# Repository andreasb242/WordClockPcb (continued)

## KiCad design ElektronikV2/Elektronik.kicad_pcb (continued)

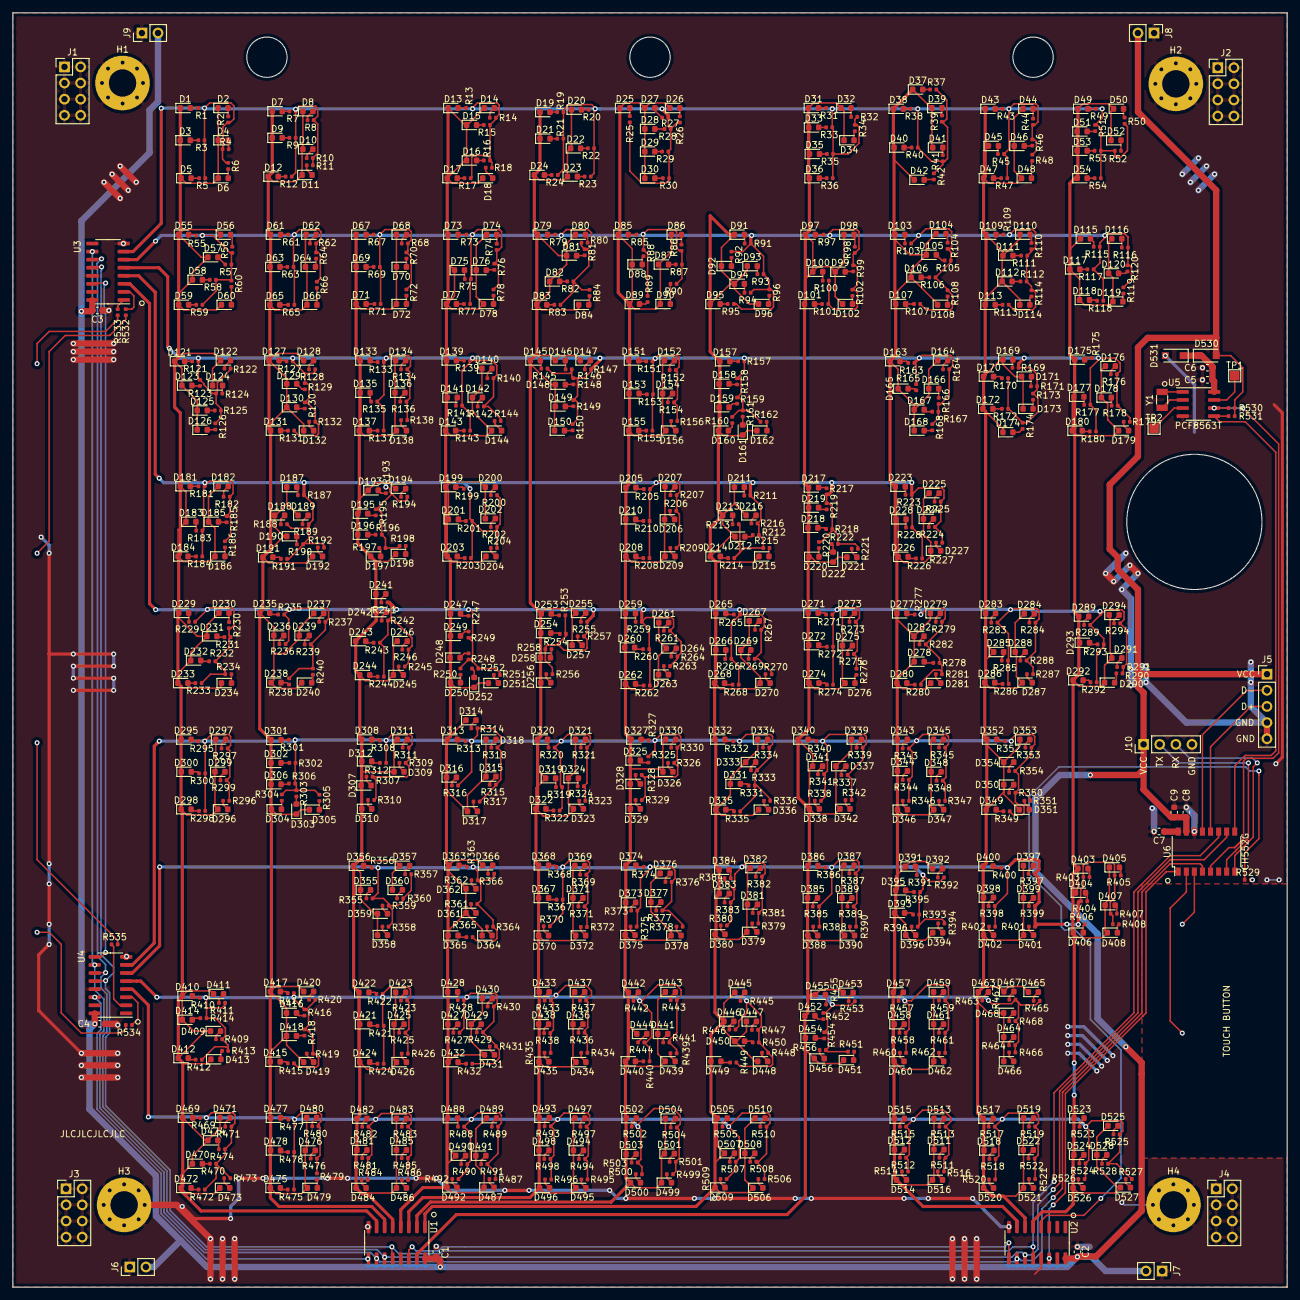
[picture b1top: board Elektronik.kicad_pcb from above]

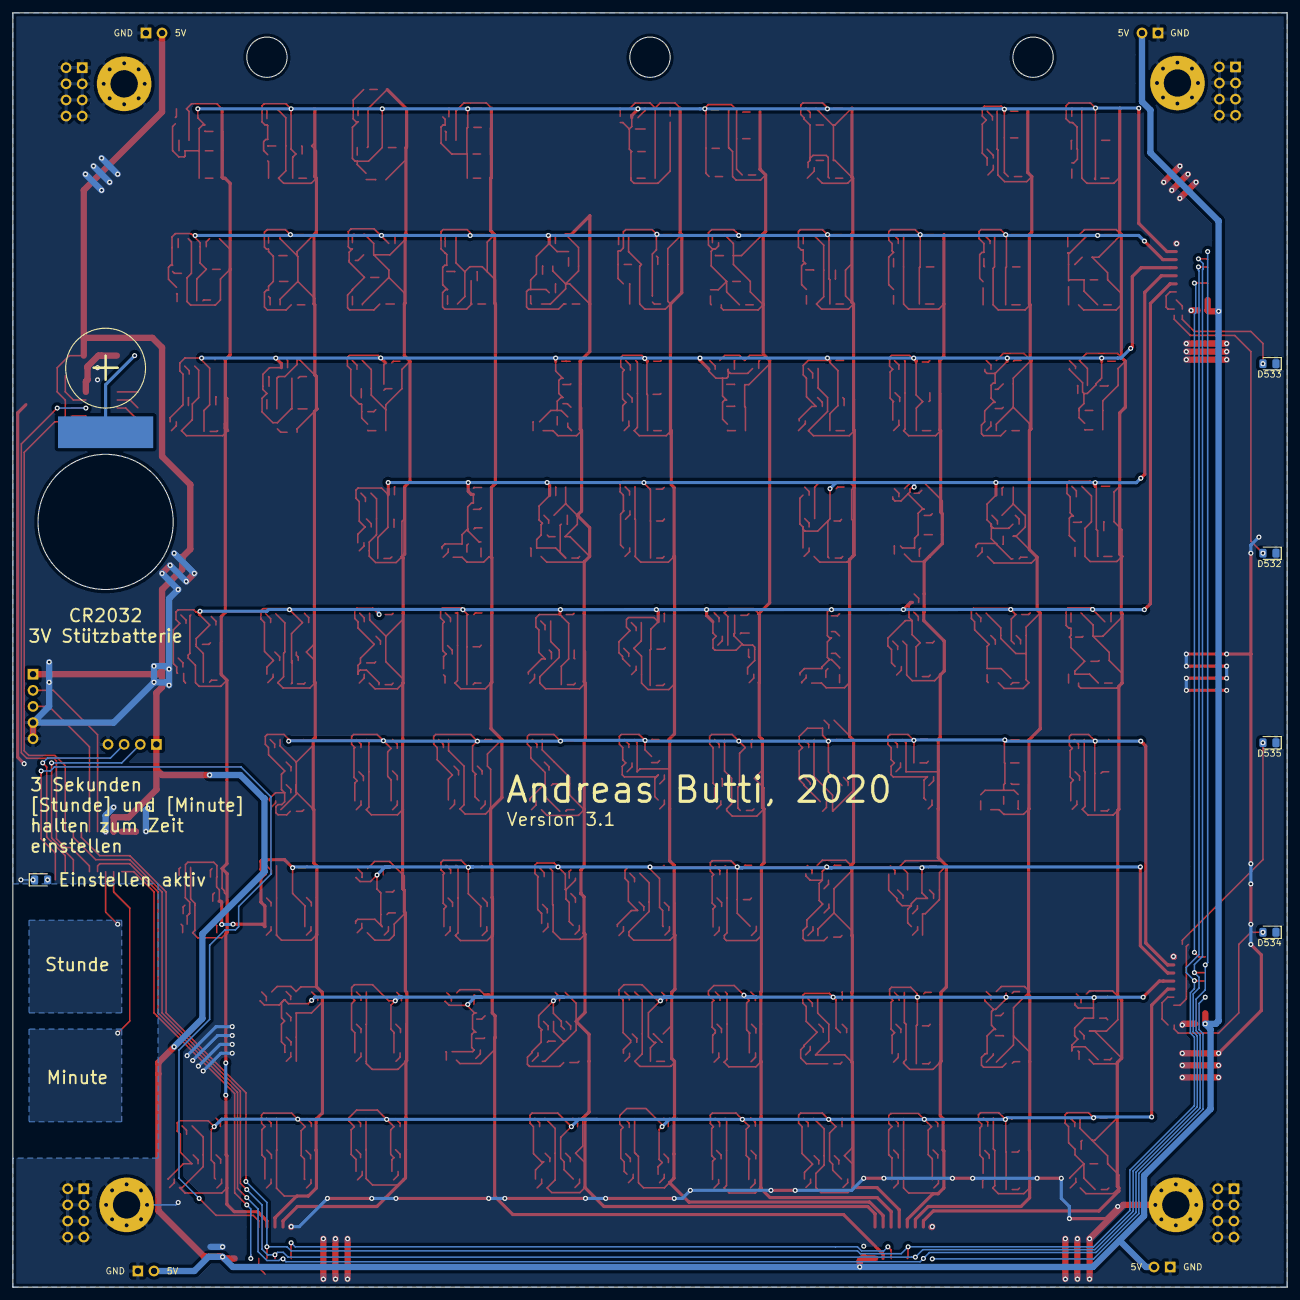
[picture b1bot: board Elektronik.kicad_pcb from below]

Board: 2 copper layers, 200.7 x 200.7 mm, 1104 parts (6 on the bottom side), 580 nets.

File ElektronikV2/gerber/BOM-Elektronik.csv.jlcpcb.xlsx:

Comment | Designator | Footprint | LCSC Part #（optional）
Conn_01x04 | J10 | PinHeader_1x04_P2.54mm_Vertical | x
1kΩ | R535,R534,R533,R532,R529 | R_0402_1005Metric | C11702
blue | D535,D534,D533,D532,D529 | LED_0805_2012Metric_Pad1.15x1.40mm_HandSolder | C72041
CH552G | U6 | SOP-16_4.4x10.4mm_P1.27mm | C111292
Conn_01x02_Male | J9,J8,J7,J6 | PinHeader_1x02_P2.54mm_Vertical | x
Conn_01x05_Male | J5 | PinHeader_1x05_P2.54mm_Vertical | x
1uF | C9,C6 | C_0603_1608Metric | C15849
100nF | C8,C7,C5,C4,C3,C2,C1 | C_0603_1608Metric | C14663
TestPoint | TP3,TP2,TP1 | TestPoint_Pad_1.5x1.5mm
Crystal | Y1 | Crystal_SMD_3215-2Pin_3.2x1.5mm
PCF8563T | U5 | SOIC-8_3.9x4.9mm_P1.27mm | C7440
4.7kΩ | R531,R530 | R_0402_1005Metric | C25900
SM4007PL | D531,D530 | D_SOD-123F | C64898
Rled | R408,R407,R406,R405,R404,R403,R528,R527,R526,R525,R524,R523,R522,R521,R520,R519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 | R_0402_1005Metric
LEDCLOCK | D408,D407,D406,D405,D404,D403,D528,D527,D526,D525,D524,D523,D522,D521,D520,D519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 | LED_0603_1608Metric
74HC595 | U4,U3,U2,U1 | SOIC-16_3.9x9.9mm_P1.27mm | C5947
MountingHole_Pad | H4,H3,H2,H1 | MountingHole_4.3mm_M4_Pad_Via | x
Conn_02x04_Counter_Clockwise | J4,J3,J2,J1 | PinHeader_2x04_P2.54mm_Vertical | x
Graphics | G2 | sw

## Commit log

2020-09-03 Initial Import for Github
2020-09-03 Fixed clock set over touch buttons
2020-09-03 Fixed 3 o'clock
2020-09-25 HW Ref 1/2 Support
2020-09-25 Board HW Ref 2 Checked in
2020-09-27 Background LEDs working
2020-09-28 Allow to switch to Bootloader with char 'b'
2020-09-30 Fixed "Eins", Version added
2020-10-17 Fixed HWREF1
2020-10-17 HW Ref 2 enabled by default
2020-11-20 Disable USB Suspend
